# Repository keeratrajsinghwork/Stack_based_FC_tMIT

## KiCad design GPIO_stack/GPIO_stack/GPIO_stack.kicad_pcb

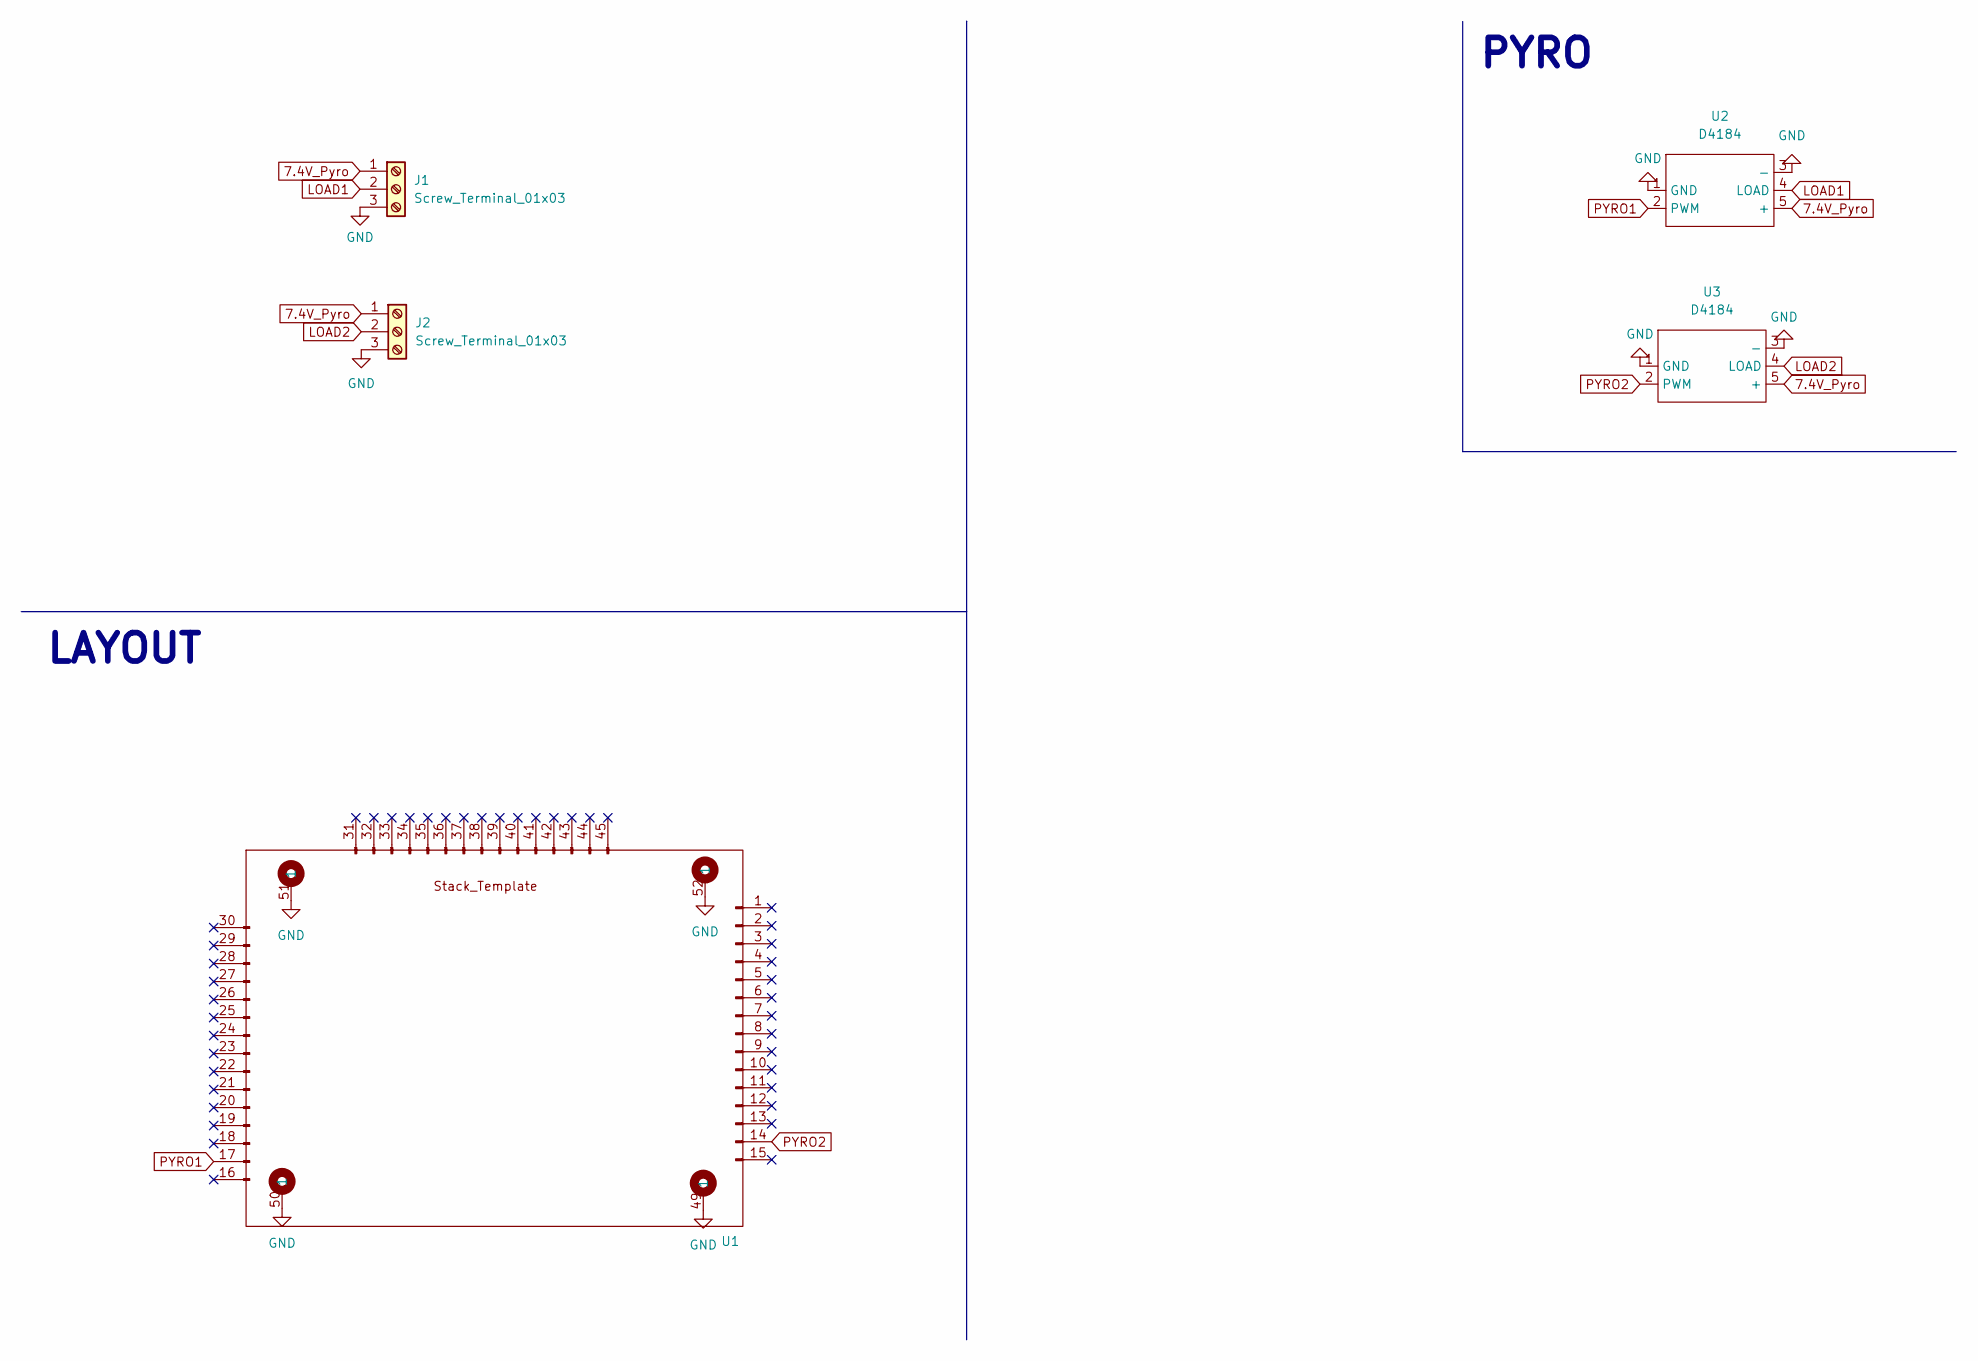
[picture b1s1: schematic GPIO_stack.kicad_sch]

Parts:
J1, J2: Screw_Terminal_01x03; TerminalBlock_bornier-3_P5.08mm
U1: FC_Stack_template
U2, U3: D4184

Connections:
7.4V_Pyro: J1.1, J2.1, U2.5 (+), U3.5 (+)
GND: J1.3, J2.3, U1.49 (1), U1.50 (1), U1.51 (1), U1.52 (1), U2.1 (GND), U2.3 (-), U3.1 (GND), U3.3 (-)
LOAD1: J1.2, U2.4 (LOAD)
LOAD2: J2.2, U3.4 (LOAD)
PYRO1: U1.17, U2.2 (PWM)
PYRO2: U1.14, U3.2 (PWM)

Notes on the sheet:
LAYOUT
PYRO

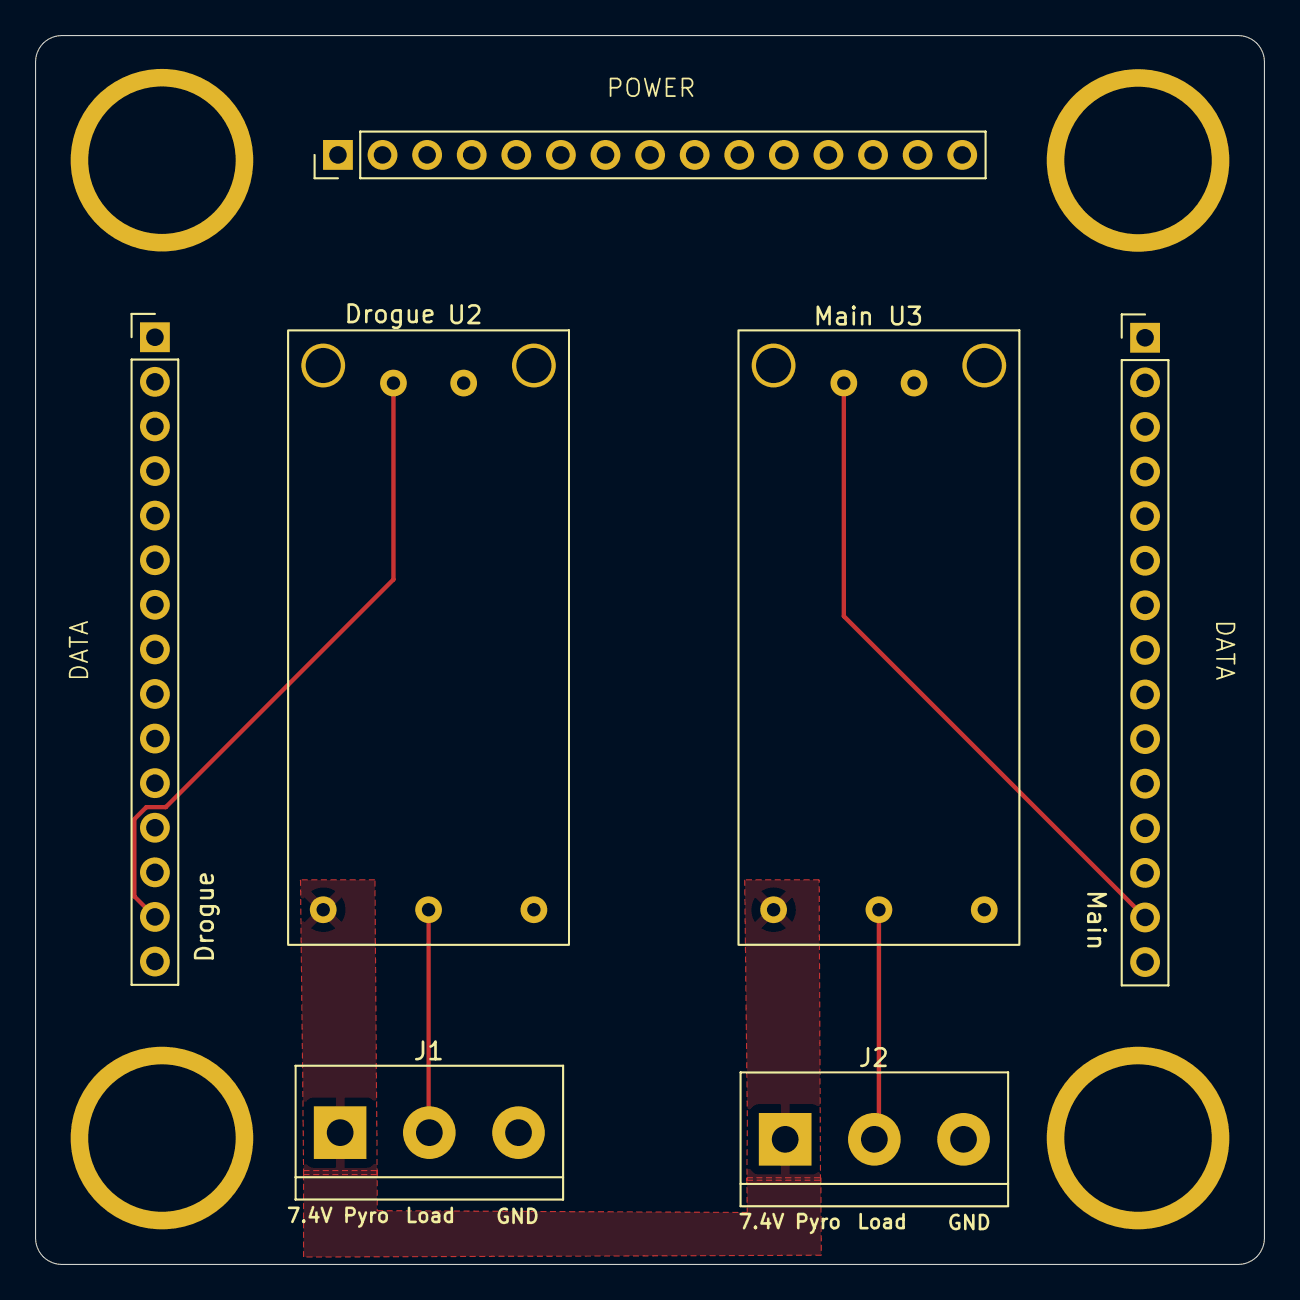
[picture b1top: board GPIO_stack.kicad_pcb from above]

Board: 2 copper layers, 70.0 x 70.0 mm, 5 parts (0 on the bottom side), 6 nets.
